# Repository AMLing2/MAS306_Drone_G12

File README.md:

# MAS306 Drone Arena 2024

<p style="text-align: center;">This repository was created for use with the bachelor thesis 2024, for the following members:</p>
<p style="text-align: center;"><i> Thomas Lønne Stiansen &nbsp; &nbsp; &nbsp; Adrian Mathias Lervik Ling &nbsp; &nbsp; &nbsp; Jan Laksesvela Haugstad</i></p>
<!-- <p style="text-align: center;"><i> Adrian Mathias Lervik Ling </i></p>
<p style="text-align: center;"><i> Jan Laksesvela Haugstad </i></p>  -->

Video from BSc. thesis, edited by Thomas Lønne Stiansen: \
https://youtu.be/jgXzDRpN-2Y?si=vNdUQDb9o-jMdF8C

## Repository Structure
- CAD ~ 3D modelling
- Canvas ~ Gathered files scattered through modules and courses
- Cheat Sheets ~ Summaries of markdown, git, etc.
- CircuitDesign ~ Electronic circuit design
- Code ~ Source Code main folder
- Datasheets ~ Relevant datasheets
- Figures ~ Temporary figures, finals are added in LaTeX.
 
## Google Docs
### Folders
- Archive ~ Old files
- Friday logs ~ Summary each week
- Weekly Muri-Meetings ~ Weekly meetings with the project mentor

### Files
- Notes MAS306
- Planning
- Gantt Chart
- System Overview

## Miscellaneous Notes
- All dates will be in the order YYYY.MM.DD
- Further README.md files may be present in sub-directories, where applicable

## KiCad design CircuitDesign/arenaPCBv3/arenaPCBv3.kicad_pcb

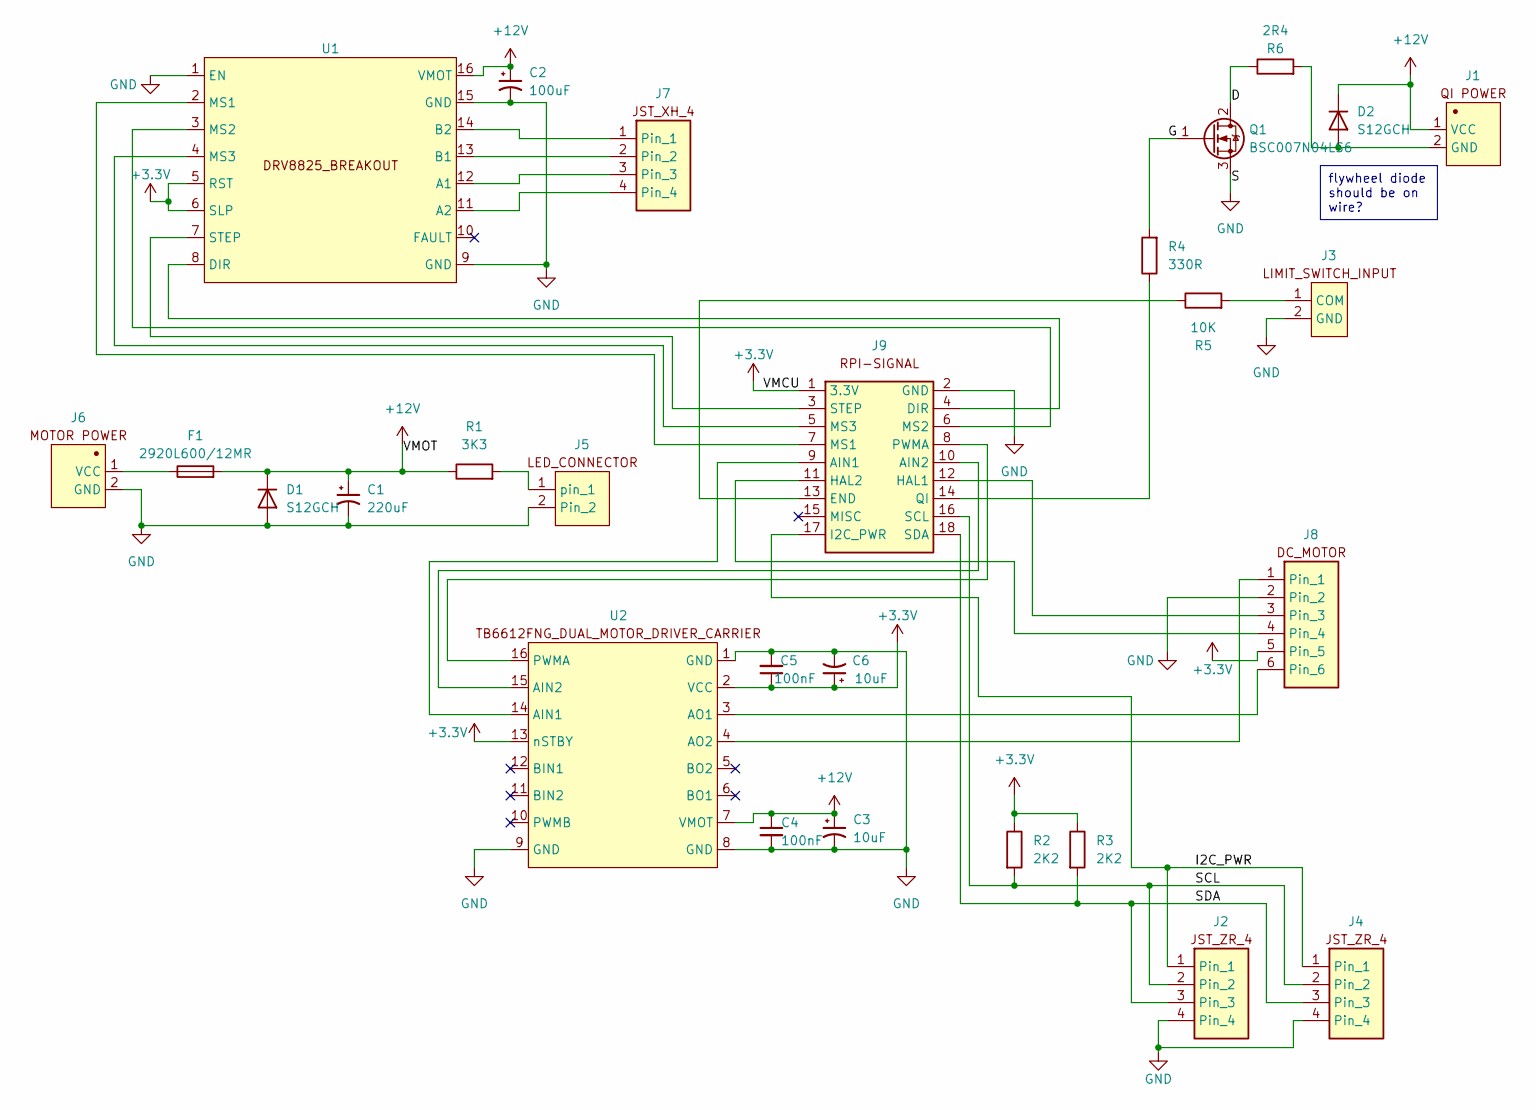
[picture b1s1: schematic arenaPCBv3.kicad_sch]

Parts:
C1: 220uF; CP_Elec_10x10.5
C2: 100uF; CP_Elec_10x10.5
C3, C6: 10uF; CP_Elec_6.3x4.5
C4, C5: 100nF; C_1210_3225Metric_Pad1.33x2.70mm_HandSolder
D1, D2: S12GCH
F1: 2920L600/12MR; Fuse_2920_7451Metric_Pad2.10x5.45mm_HandSolder
J1: CONN_MTA_100_2
J2, J4: B4B-ZR-SM4-TFT
J3: B2B-ZR-SM4-TFT
J5: led_header_p2.54_2pin
J6: TERMINAL_BLOCK_5081
J7: CONN_MTA_100_4
J8: CONN_MTA_100_6
J9: CONN_MOLEX_18p_2.00mm
Q1: BSC007N04LS6; PG-TDSON-8-6_INF
R1: 3K3; R_2512_6332Metric_Pad1.40x3.35mm_HandSolder
R2, R3: 2K2; R_1210_3225Metric_Pad1.30x2.65mm_HandSolder
R4: 330R; R_1210_3225Metric_Pad1.30x2.65mm_HandSolder
R5: 10K; R_1210_3225Metric_Pad1.30x2.65mm_HandSolder
R6: 2R4; R_1210_3225Metric_Pad1.30x2.65mm_HandSolder
U1, U2: CONN_BREAKOUT_BOARDS

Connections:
+3.3V: C5.1, C6.1, J8.5, J9.1 (3.3V), R2.1, R3.1, U1.5 (RST), U1.6 (SLP), U2.2 (VCC), U2.13 (nSTBY)
+12V: C1.1, C2.1, C3.1, C4.1, D1.1 (K), D2.1 (K), F1.2, J1.1 (VCC), R1.1, U1.16 (VMOT), U2.7 (VMOT)
/G: Q1.1 (G), R4.2
/I2C_PWR: J2.1, J4.1, J9.17 (I2C_PWR)
/SCL: J2.2, J4.2, J9.16 (SCL), R2.2
/SDA: J2.3, J4.3, J9.18 (SDA), R3.2
GND: C1.2, C2.2, C3.2, C4.2, C5.2, C6.2, D1.2 (A), J2.4, J3.2 (GND), J4.4, J5.2, J6.2 (GND), J8.2, J9.2 (GND), Q1.3 (S), U1.1 (EN), U1.9 (GND), U1.15 (GND), U2.1 (GND), U2.8 (GND), U2.9 (GND); also elsewhere on the board
unnamed: J3.1 (COM), J9.13 (END), R5.1, R5.2
unnamed: J5.1 (pin), R1.2
unnamed: F1.1, J6.1 (VCC)
unnamed: J7.1, U1.14 (B2)
unnamed: J7.2, U1.13 (B1)
unnamed: J7.3, U1.12 (A1)
unnamed: J7.4, U1.11 (A2)
unnamed: J8.1, U2.4 (AO2)
unnamed: J8.3, J9.12 (HAL1)
unnamed: J8.4, J9.11 (HAL2)
unnamed: J8.6, U2.3 (AO1)
unnamed: J9.9 (AIN1), U2.14 (AIN1)
unnamed: J9.10 (AIN2), U2.15 (AIN2)
unnamed: J9.4 (DIR), U1.8 (DIR)
unnamed: J9.7 (MS1), U1.2 (MS1)
unnamed: J9.6 (MS2), U1.3 (MS2)
unnamed: J9.5 (MS3), U1.4 (MS3)
unnamed: J9.8 (PWMA), U2.16 (PWMA)
unnamed: J9.14 (QI), R4.1
unnamed: J9.3 (STEP), U1.7 (STEP)

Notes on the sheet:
flywheel diode should be on wire?

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
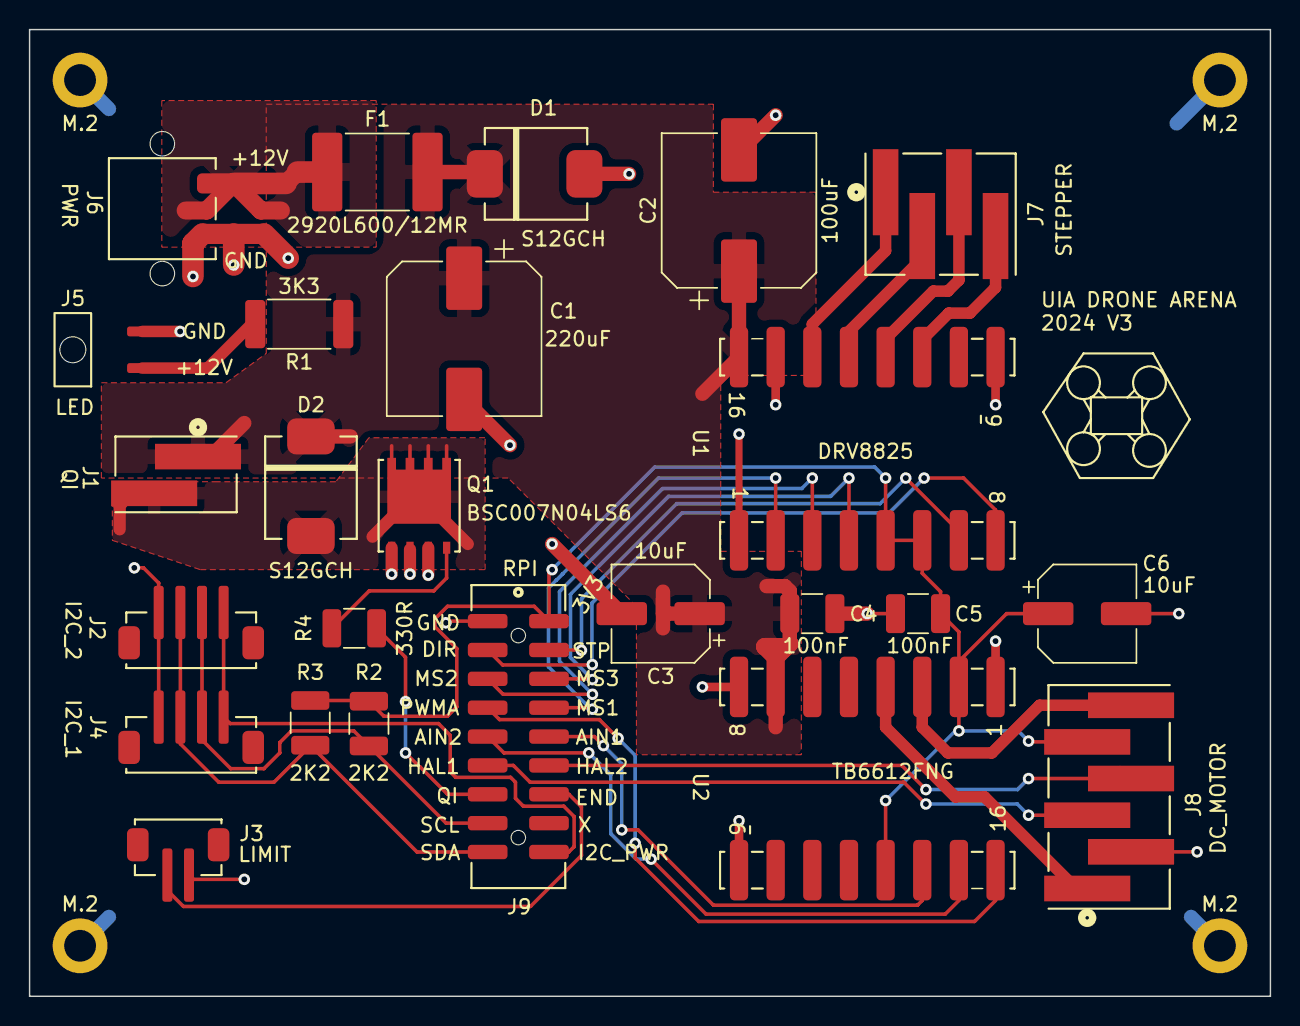
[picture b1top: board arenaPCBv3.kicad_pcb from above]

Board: 2 copper layers, 86.0 x 67.0 mm, 29 parts (0 on the bottom side), 28 nets.

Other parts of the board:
M,2: MountingHole_2.2mm_M2_DIN965_Pad
M.2, M.2#2, M.2#3: MountingHole_2.2mm_M2_DIN965_Pad

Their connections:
GND: M,2.1, M.2.1, M.2#2.1, M.2#3.1; also elsewhere on the board

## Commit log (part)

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2024-01-09 initial commit 2
2024-01-09 Added folder system
2024-01-09 Added Prosjektfordeling rev3
2024-01-17 kakute F4V2 datasheet
2024-01-19 Uploaded explanation Figures.
2024-01-24 added code folder
2024-01-24 Uploaded Python test and Facial Recognition
2024-01-29 Added containers cheat sheet, framework overview (png)
2024-01-29 Added README for Camera, also screenshot script
2024-01-30 Update ArUco script: colors, ID text++
2024-01-31 Updated ID display
2024-01-31 Uploaded semi-working calibration. With images that worked, pre-floor pics
2024-02-07 Added test line, for checking git user
2024-02-07 Reorganized Camera directory
2024-02-08 removed bag file that caused issues.
2024-02-09 Updated 'Camera' directory and specific README
2024-02-09 recordingReader now working with multiple markers (laggy). Also removed pickle from stateEstimate
2024-02-09 circuit diagram finished before adding component values
2024-02-12 Added results dir and copied results from enumerate. Updated README.
2024-02-13 PCB v1 finished
2024-02-13 Moved results to correct folder (json). Removed destroyAllWindows method from test, now default script.
2024-02-14 Added screenshots with grey formats for color camera.
2024-02-14 Added screenshots also with IR. Revised screenshotCamera.py
2024-02-14 Updated code with color mapped depth and also added depth screenshots.
2024-02-14 Final update tuesday
2024-02-15 Removed old inspired by text, no longer applicable for screenshotCamera.py
2024-02-15 Updated arucoDetector.py
2024-02-15 Updated dir missing in arucoDetection
2024-02-15 Updated screenshotCamera and arucoDetection to be synced with report and each other
2024-02-16 Before redoing PCB
2024-02-16 IR test 2
2024-02-16 IR test 4
2024-02-16 Revised recording without bag files
2024-02-16 Merged recordingVidWriter and updated git_commands
2024-02-19 Added recordingReaderAll.py, dupe from recordingReader.py atm. Currently reads all markes in video, latter will only read one at a time and export in the future
2024-02-19 Updated recReader, now one dict at a time. Also updated readme, moved csv file and recReaderAll
2024-02-19 pcb done before changing diodes and C1
2024-02-19 Renamed recordingReader -> markerTestAnalyzer with all 3 working (probably, need to confirm after restoring video capture from previous version of this file)
2024-02-19 Cleaner code
2024-02-19 Updated readme again, with vid on drive
2024-02-19 pcb finished v2
2024-02-19 Added updated arucoPoseEstimate pre-multi marker trackin
2024-02-19 Removed csv-integration and related csv results, as they proved redundant.
2024-02-19 cv2.aruco --> aruco
2024-02-20 Added regression test from MATLAB
2024-02-20 Added screenshot from Calibration Tool Print Target
2024-02-20 Updated for working cameraCalibration, as well as updated screenshotCamera for directory and readme update.
2024-02-20 Working with 160 cm pretty darn good. With aruco 7x7 50mm (really 51)
2024-02-21 Added final BEST lengt test
2024-02-21 Removed excess intrinsics. Now only SDK and OpenCV v2 remains
2024-02-21 Updated camera calibration to display images for 250 ms
2024-02-21 Updated calibration script, also with exported results.
2024-02-26 Updated with comments, also no more new object with subPix, as it pass by reference
2024-02-26 Moved markerDistTest to Results and cleaned. Hopefully
2024-02-26 removed GPT tip, not applicable
2024-02-27 Added depth reading
2024-02-27 Added recursive filter to depth. Maybe remove
2024-02-28 Added working C++ code with cmake in VS Code. Both OpenCV and Librealsense (realsense in other file)
2024-02-28 pcb updates and other stuff
2024-02-28 Prettified hybrid pose estimator
2024-03-01 Added CAD, QualisysMarkerCube and updated main readme
2024-03-01 Updated depth frame scripts
2024-03-01 Removed pylance link in combo
2024-03-01 SMD PCB done
2024-03-04 Updated with tilted axes and updated readme
2024-03-06 Updated plot with both, WIP with axis flipping
2024-03-08 Added double axes frames for dispaly and compare to matlab sim
2024-03-20 Added both correct cube and skewed planes, pre-printing in ABS or APA for QualisysMarkerCube
2024-03-21 2022 Flight controller project files
2024-03-22 ros2 packages, encoder
2024-04-03 Went back to time.time() for analyzer, also removed pyrealsense library from both
2024-04-03 Exported new flattened csv file
2024-04-03 Added subpixel detection for pose, overwritten txt/csv
2024-04-04 Removed redundant line in analyzer, also still WIP with poseMarkerDepth. Pre-reroll
2024-04-04 estimatePoseSingleMarkers now used, also logging rotVector
2024-04-04 Brute force testing with flipping vector logic
2024-04-04 [Experimental] WIP workaround from git. To-be-removed
2024-04-05 [Working] Added iterative ExtrinsicGuess with SolvePnPgeneric()
2024-04-05 communication and protobuf updates
2024-04-05 update to drone to main communication
2024-04-05 final update for today. Working with extrinsicguess and another dict
2024-04-08 Currently SolvePnPGeneric with SOLVPNP_IPPE multiple solutions. Also exported results from analyzer
2024-04-08 Dict test arena #2. Also updated poseMarkerDepth with working 5x5 iterative
2024-04-08 Cleaned code and added timer
2024-04-08 Final update for today, added proto stuffs in bottom for Adrian
2024-04-08 drone client update
2024-04-09 updated proto message
2024-04-09 Arena CAD files
2024-04-10 files added
2024-04-10 Added dxf post-laser cut
2024-04-10 Added Qualisys test Initializer script
2024-04-11 qualisys test start
2024-04-11 2022 Drone Arena CAD files
2024-04-11 updated qualisys test
2024-04-11 Cleaned up in CAD folders. Also added CAD readme and new assembly. Still missing rods, so pre-Frustum.
2024-04-12 Measured and added rods..
2024-04-12 updated qualisys test for camera only
2024-04-12 Updated code, now incrementing correctly with video and csv to folder in home. Also cleaned folder up
2024-04-12 added CAD drawings
2024-04-13 Updated now with corrected translation. TBA rotation transformation and start for qualisys data
2024-04-13 Cleaner code, synchronized by translation movement
2024-04-15 WIP time syncher
2024-04-15 fixing protobuf compilation
2024-04-15 protobuf functional with c++ test code
2024-04-15 Added matlab plotting and Added plane for Qualisys orientation of 6DOF frame
2024-04-16 Export of rotMatElements
2024-04-16 Revert "python servercode updated"
    This reverts commit 195e80b3f03fa7ee9a5b19a2cad8b92eb4fe34c8.
2024-04-16 Added rotMat comparison matlab
2024-04-16 backup scary
2024-04-16 Added rest of test results in csv from 16.4.2024
2024-04-16 MATLAB plotting prettified
2024-04-17 Split code, WIP poseTestAnalysis
2024-04-17 Updated with export from poseTestAnalysis.py
2024-04-17 Updated more correct indexing, hopefully
2024-04-17 Seems to work like before*
2024-04-17 threading and rt start
2024-04-18 Added ExportedResults from 17.4.2024 to qualisysTest folder
2024-04-18 somewhat fixed segfault error
2024-04-18 cleaned up code
2024-04-19 Removed .asv file
2024-04-19 Removed 0-frames on all plots and prettyfied plots/code.
2024-04-19 Updated so now plots all 3 combos of angle in XY projection. Only one diff, tba 2 more
2024-04-19 Updated import/export with variable automatically
2024-04-19 starting full server implementation
2024-04-22 Added updated plotting and kalman filter folder
2024-04-23 initial implementation of server
2024-04-24 start of implementing sockets to camera code
2024-04-24 camera code updated to send data, untested, protoc needs updating
2024-04-25 camera code update
2024-04-25 Updated Kalman 1D WIP, pre-acc combo
2024-04-25 camera sending code functional
2024-04-25 1D Kalman filter working ok with very high R and only measuring position from camera
2024-04-26 Updated KalmanFilter1D with temporal interpolation of QTM. Still overshoot.
2024-04-26 Updated filter, now only update measurement when detected
2024-04-27 Cleaner 1D kalman filter code
2024-04-27 Updated 1D filter pre-noise
2024-04-27 Added noise to IMU sim. Pre-corrected from datasheet, which also is added in this commit
2024-04-28 Added script for distribution fitting, currently only plotting all translations
2024-04-28 WIP dists, pre-machine learning toolbox
2024-04-28 Updated with distributions for all intervals, as well as stdDev variable implemented in filter
2024-04-29 Updated 3D kalman filter working with static distributions
2024-04-29 Added colors outside \pm 1sigma, also made dots smaller for readability
2024-04-30 start of spi imu reading, needs calibration
2024-04-30 Added polynomial fits for all 3 translations
2024-05-03 Updated with corrected nx1 y-vecotr
2024-05-03 Uploaded video editing ShotCut. 87 kB, only editing file, not videos
2024-05-06 Added Frustum Display finished with assembly
2024-05-06 removed redundant line
2024-05-06 tiny server update
2024-05-07 Removed redundant font-lines in analzyer
2024-05-07 Added calib plate sketch
2024-05-07 Added drawing of topStick as well for qualisystest
2024-05-08 Removed cameraCenter unused lines, cleaner code.
2024-05-08 drone imu sending very close to finished
2024-05-08 Cleaned Aruco Export
2024-05-08 Removed unused line
2024-05-08 pushing befure updating the protobuf msg breaks every script
2024-05-08 updated imu reading for new protobuf, cleaned up build files
2024-05-09 Moved test file to old folder
2024-05-09 Updated names for assemblies, to separate this years files
2024-05-09 Cleanedd translations, WIP rest cleaning. Also added comparison of transVector1 to QTM
2024-05-09 Updated MAD calcs for trans vectors. (also slight in axis-angle plot, WIP)
2024-05-10 Added frontpage figure with quadcopter, from paint.net combo. Also added arucoPlate part for simpler visualisation of skew projection for image
2024-05-10 Cleaned last part of xy-projection, also fixed validIndices
2024-05-10 Modified to hybrid Modulo, now check for both due to difference in placement of them
2024-05-10 server finished without HMI (terminal)
2024-05-12 Added polynomial plots and code after adding to report
2024-05-12 Updated kalman filters
2024-05-13 Updated with startTime and stopTime for difference statistics
2024-05-13 Changed mad to non-mad
2024-05-13 Updated 3D to match 1D
2024-05-13 Updated with confidence intervals of abs(error) plots for x and y
2024-05-14 Added P-filament specs, translated and listed from datasheet
2024-05-16 Updated with material, WIP skrogbunn drawing
2024-05-16 Updated bottom, almost finished.
2024-05-16 Fixed language logo, WIP top
2024-05-18 new CAD parts for actuator
2024-05-18 Updated tech drawings, pre-check 18-5-2024_15-51
2024-05-18 WIP drawings pre-usb on other pc
2024-05-18 encoder reading
2024-05-19 Updated footprint drawing and added main readme for code
2024-05-19 Cleaned folder and removed temp files. Post rm recursive. Also gitignore added WIP content
2024-05-19 Added full assembly and made M2x5 and x8 screws
2024-05-19 Fully defined assembly w/o circuit
2024-05-19 Added drone-4
2024-05-19 updated buttonblock and magnet holder
2024-05-19 Checkpoint after inspection for drone and poseTest, missing arena
2024-05-19 Drawings arena 19.5 report
2024-05-20 Updated corrected drone-3 with less zeros and added circumference on arm holes
2024-05-20 Added block diagrams from draw.io, w/o rescaling by TLS
2024-05-20 Updated with correct font and size for overview block diagram
2024-05-21 Added CFD simulation result plotting
2024-05-21 (adrian) updated camera code
2024-05-21 updated drone client
2024-05-21 update to main cv code
2024-05-21 (adrian) final camera code
2024-05-21 (Adrian) cleaned up cv code
2024-05-21 CFD result plotting
2024-05-22 Updated with removed kalman filter redundant CV=0 check
2024-05-22 wiringpi test
2024-05-23 updates to imuonly code
2024-05-23 2022 Drone Cad
